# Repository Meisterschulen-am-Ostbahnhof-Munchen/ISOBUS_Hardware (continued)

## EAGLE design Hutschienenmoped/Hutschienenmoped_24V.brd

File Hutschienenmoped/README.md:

## Hutschienenmoped

<p xmlns:cc="http://creativecommons.org/ns#" xmlns:dct="http://purl.org/dc/terms/"><a property="dct:title" rel="cc:attributionURL" href="https://github.com/Meisterschulen-am-Ostbahnhof-Munchen/ISOBUS_Hardware">Hutschienenmoped</a> by <a rel="cc:attributionURL dct:creator" property="cc:attributionName" href="https://github.com/Meisterschulen-am-Ostbahnhof-Munchen">Meisterschulen am Ostbahnhof, München</a> is licensed under <a href="https://creativecommons.org/licenses/by-sa/4.0/?ref=chooser-v1" target="_blank" rel="license noopener noreferrer" style="display:inline-block;">CC BY-SA 4.0</a></p>

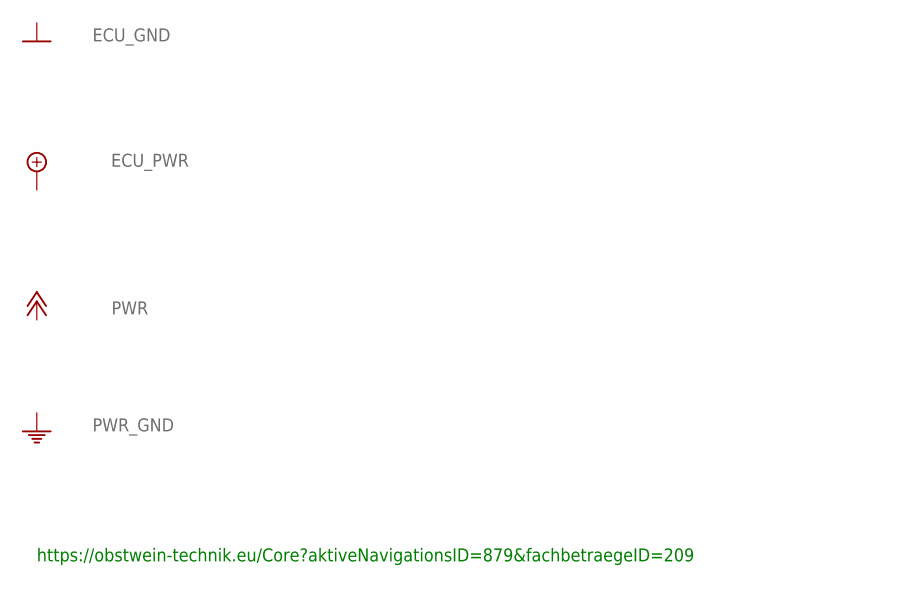
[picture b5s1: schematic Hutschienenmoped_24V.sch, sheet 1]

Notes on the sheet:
https://obstwein-technik.eu/Core?aktiveNavigationsID=879&fachbetraegeID=209

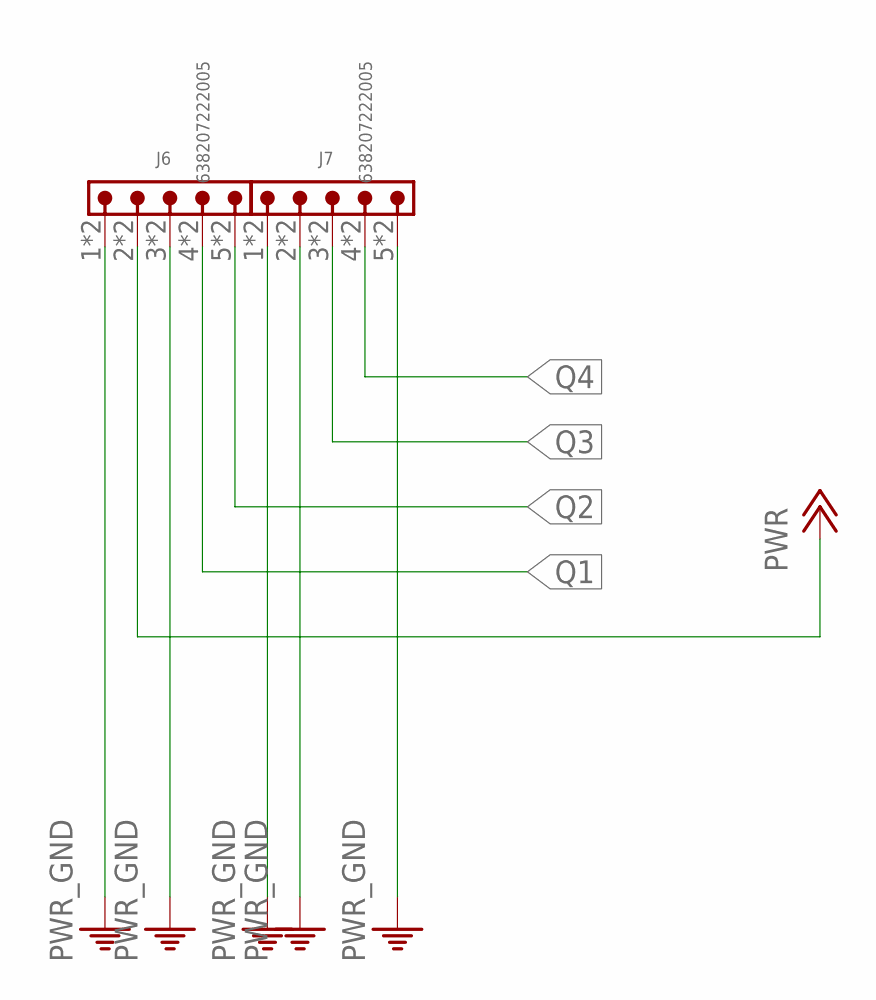
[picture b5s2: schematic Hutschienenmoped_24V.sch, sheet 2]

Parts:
J6, J7: 638207222005

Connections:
PWR: J6.2, J6.A2 (2); also elsewhere on the board
PWR_GND: J6.1, J6.3, J6.A1 (1), J6.A3 (3), J7.1, J7.2, J7.5, J7.A1 (1), J7.A2 (2), J7.A5 (5); also elsewhere on the board
Q1: J6.4, J6.A4 (4); also elsewhere on the board
Q2: J6.5, J6.A5 (5); also elsewhere on the board
Q3: J7.3, J7.A3 (3); also elsewhere on the board
Q4: J7.4, J7.A4 (4); also elsewhere on the board

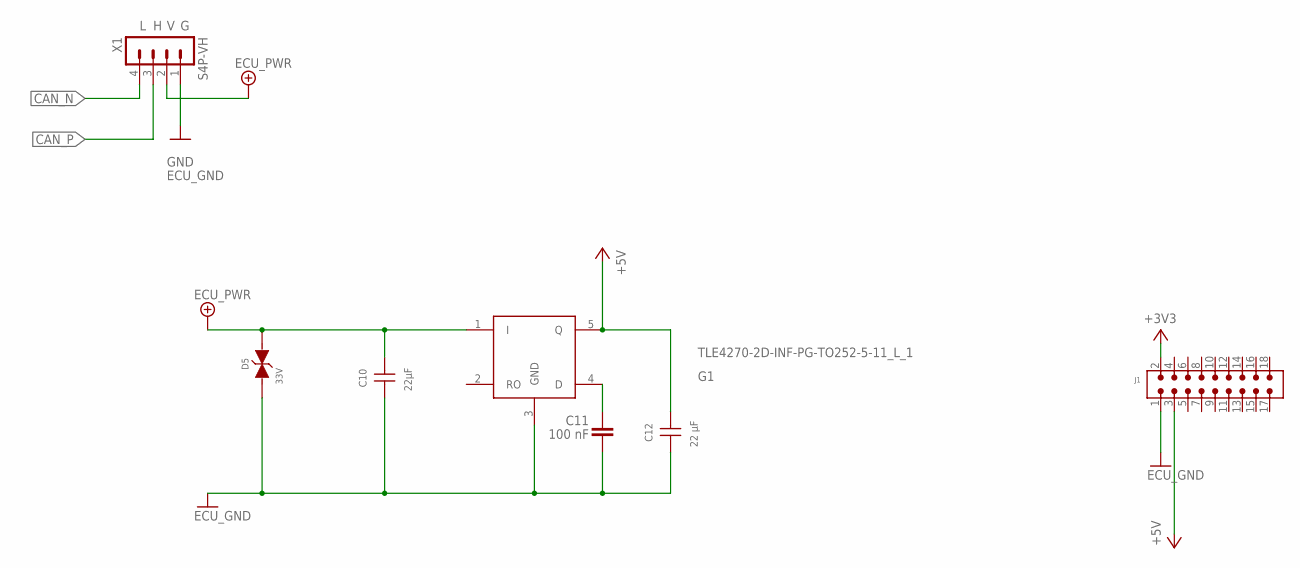
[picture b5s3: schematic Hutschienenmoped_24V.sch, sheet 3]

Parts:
C10: 22µF; WCAP-CSGP_1210_H2.5
C11: 100 nF; WCAP-CSGP_0402
C12: 22 µF; WCAP-CSGP_0805_H1.25_R
D5: 33V; WE-TVSP_DO-214AB_BIDIRECTIONAL
G1: TLE4270-2D-INF-PG-TO252-5-11_L_1; INF-PG-TO252-5-11_L_1PRIMARY
J1: 6130XX21121_61301821121; 61301821121
X1: S4P-VH

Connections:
+3V3: J1.2; also elsewhere on the board
+5V: C12.2, G1.5 (Q), J1.3; also elsewhere on the board
CAN_N: X1.4; also elsewhere on the board
CAN_P: X1.3; also elsewhere on the board
ECU_GND: C10.1, C11.2, C12.1, D5.1, G1.3 (GND), J1.1, X1.1; also elsewhere on the board
ECU_PWR: C10.2, D5.2, G1.1 (I), X1.2; also elsewhere on the board
unnamed: C11.1, G1.4 (D)

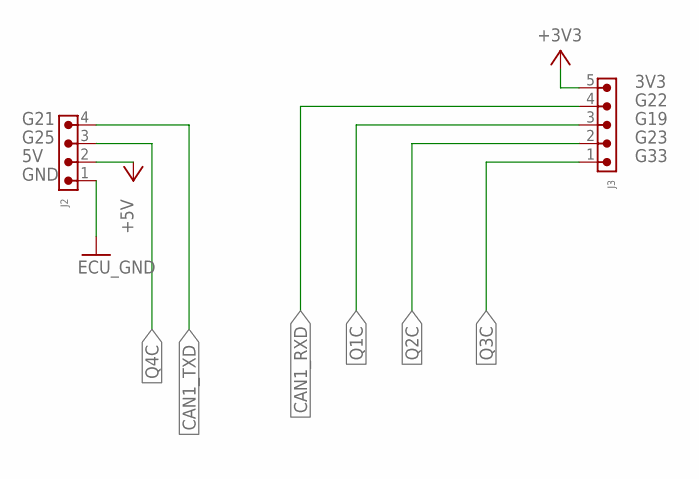
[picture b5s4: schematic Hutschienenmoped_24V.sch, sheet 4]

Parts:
J2: 6130XX11121_61300411121; 61300411121
J3: 6130XX11121_61300511121; 61300511121

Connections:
+3V3: J3.5; also elsewhere on the board
+5V: J2.2; also elsewhere on the board
CAN1_RXD: J3.4; also elsewhere on the board
CAN1_TXD: J2.4; also elsewhere on the board
ECU_GND: J2.1; also elsewhere on the board
Q1C: J3.3; also elsewhere on the board
Q2C: J3.2; also elsewhere on the board
Q3C: J3.1; also elsewhere on the board
Q4C: J2.3; also elsewhere on the board

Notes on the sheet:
GND
G25
G21
G33
G23
G19
G22
3V3

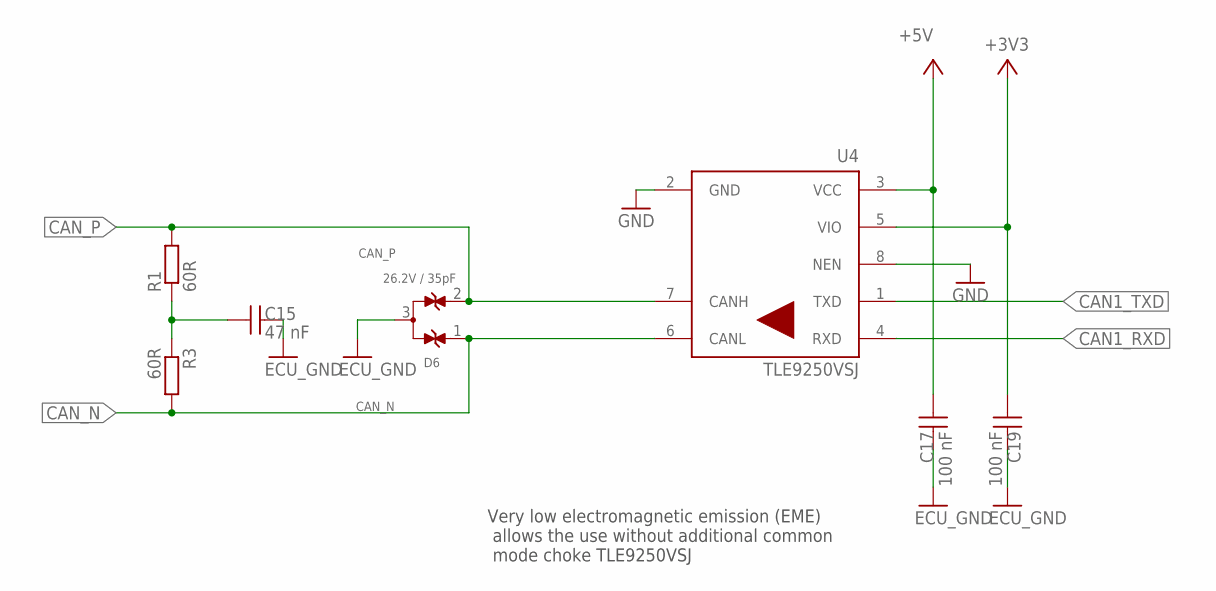
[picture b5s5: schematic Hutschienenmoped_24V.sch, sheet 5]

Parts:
C15: 47 nF; WCAP-CSGP_0805_H0.8_R
C17, C19: 100 nF; WCAP-CSGP_0805_H0.8_R
D6: 26.2V / 35pF; WE-TVS_SOT23-3L
R1, R3: 60R; R0805
U4: TLE9250VSJ; SOIC127P602X173-8N-V

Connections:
+3V3: C19.1, U4.5 (VIO); also elsewhere on the board
+5V: C17.1, U4.3 (VCC); also elsewhere on the board
CAN1_RXD: U4.4 (RXD); also elsewhere on the board
CAN1_TXD: U4.1 (TXD); also elsewhere on the board
CAN_N: D6.1, R3.2, U4.6 (CANL); also elsewhere on the board
CAN_P: D6.2, R1.2, U4.7 (CANH); also elsewhere on the board
ECU_GND: C15.2, C17.2, C19.2, D6.3, U4.2 (GND), U4.8 (NEN); also elsewhere on the board
unnamed: C15.1, R1.1, R3.1

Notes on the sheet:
Very low electromagnetic emission (EME) allows the use without additional common mode choke TLE9250VSJ

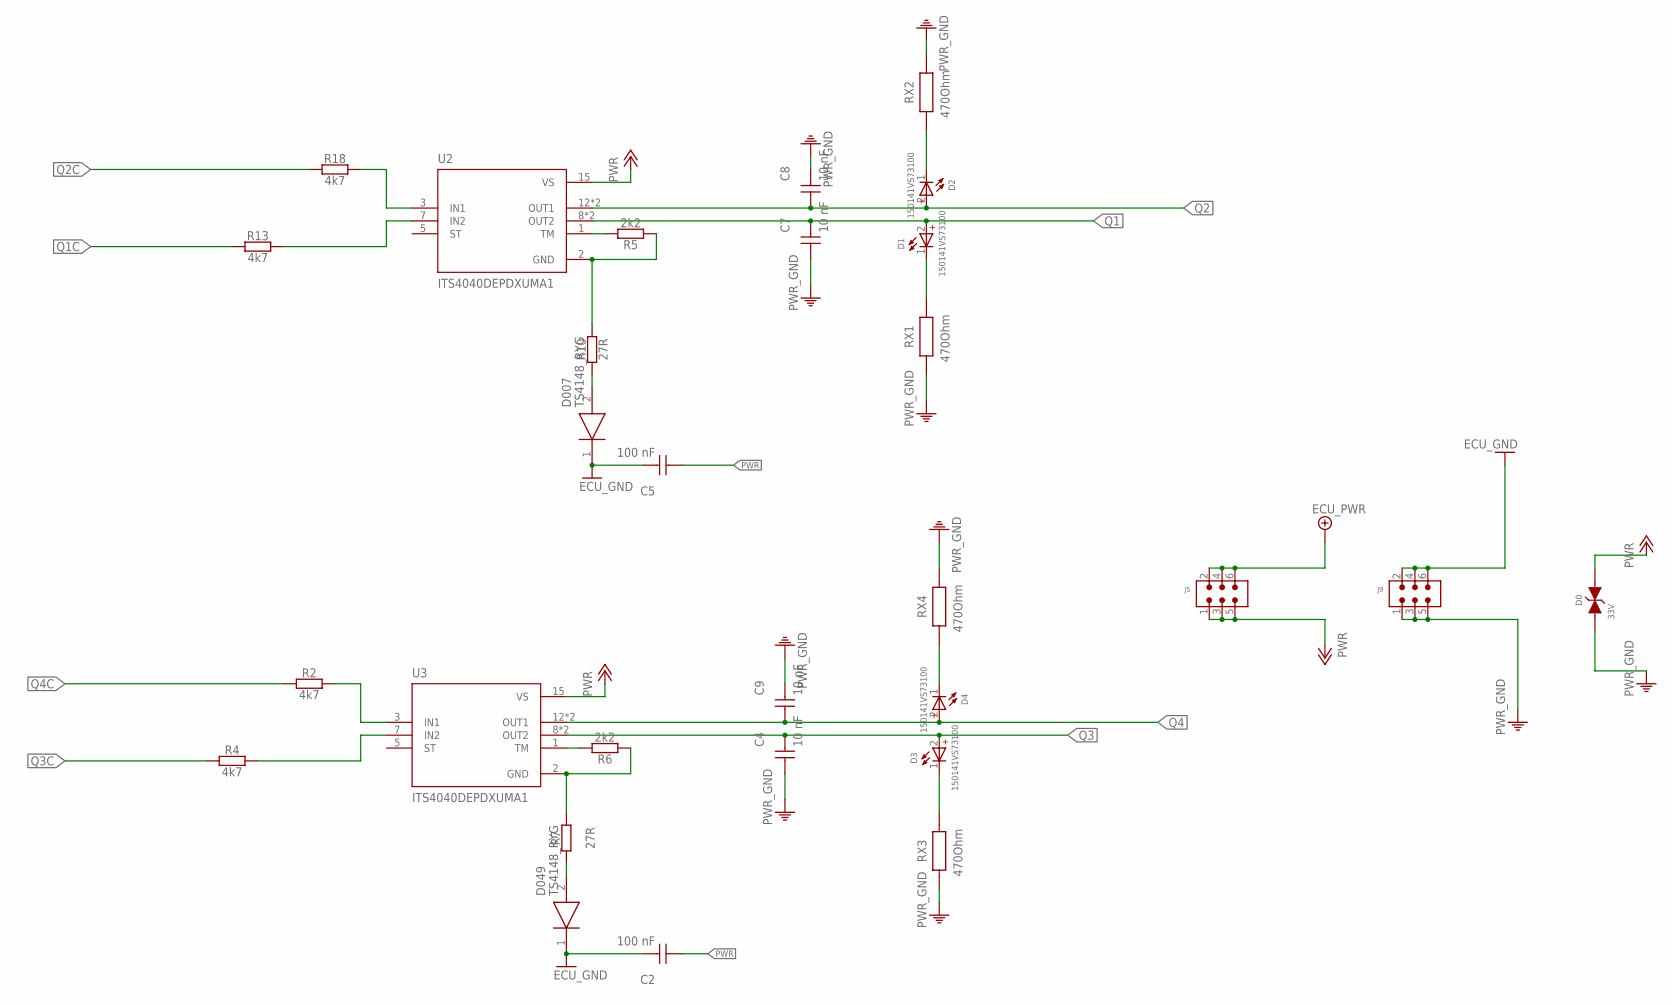
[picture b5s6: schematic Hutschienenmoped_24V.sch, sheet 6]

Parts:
C2, C5: 100 nF; WCAP-CSGP_0805_H0.8_R
C4, C7, C8, C9: 10 nF; WCAP-CSGP_0805_H0.8_R
D0: 33V; WE-TVSP_DO-214AB_BIDIRECTIONAL
D1, D2, D3, D4: 150141VS73100; WL-SMTW_3528
D007, D049: TS4148_RYG; DIOC2012X95N
J5, J9: 6130XX21121_61300621121; 61300621121
R2, R4, R13, R18: 4k7; R0805
R5, R6: 2k2; R0805
R7, R10: 27R; R0805
RX1, RX2, RX3, RX4: 470Ohm; WRIS-KWKB_0612
U2, U3: ITS4040DEPDXUMA1; SOP65P600X115-15N

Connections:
ECU_GND: C2.2, C5.2, D007.1 (K), D049.1 (K), J9.2, J9.4, J9.6; also elsewhere on the board
ECU_PWR: J5.2, J5.4, J5.6; also elsewhere on the board
unnamed: D4.1 (-), RX4.1
unnamed: R2.2, U3.3 (IN1)
unnamed: R6.2, U3.1 (TM)
unnamed: R4.2, U3.7 (IN2)
unnamed: R5.2, U2.1 (TM)
unnamed: D2.1 (-), RX2.1
unnamed: D1.1 (-), RX1.2
unnamed: D3.1 (-), RX3.2
unnamed: R18.2, U2.3 (IN1)
unnamed: D049.2 (A), R7.1
unnamed: D007.2 (A), R10.1
unnamed: R6.1, R7.2, U3.2 (GND)
unnamed: R13.2, U2.7 (IN2)
unnamed: R5.1, R10.2, U2.2 (GND)
PWR: C2.1, C5.1, D0.2, J5.1, J5.3, J5.5, U2.15 (VS), U3.15 (VS); also elsewhere on the board
PWR_GND: C4.1, C7.1, C8.2, C9.2, D0.1, J9.1, J9.3, J9.5, RX1.1, RX2.2, RX3.1, RX4.2; also elsewhere on the board
Q1: C7.2, D1.2 (+), U2.8 (OUT2), U2.10 (OUT2); also elsewhere on the board
Q1C: R13.1; also elsewhere on the board
Q2: C8.1, D2.2 (+), U2.12 (OUT1), U2.14 (OUT1); also elsewhere on the board
Q2C: R18.1; also elsewhere on the board
Q3: C4.2, D3.2 (+), U3.8 (OUT2), U3.10 (OUT2); also elsewhere on the board
Q3C: R4.1; also elsewhere on the board
Q4: C9.1, D4.2 (+), U3.12 (OUT1), U3.14 (OUT1); also elsewhere on the board
Q4C: R2.1; also elsewhere on the board

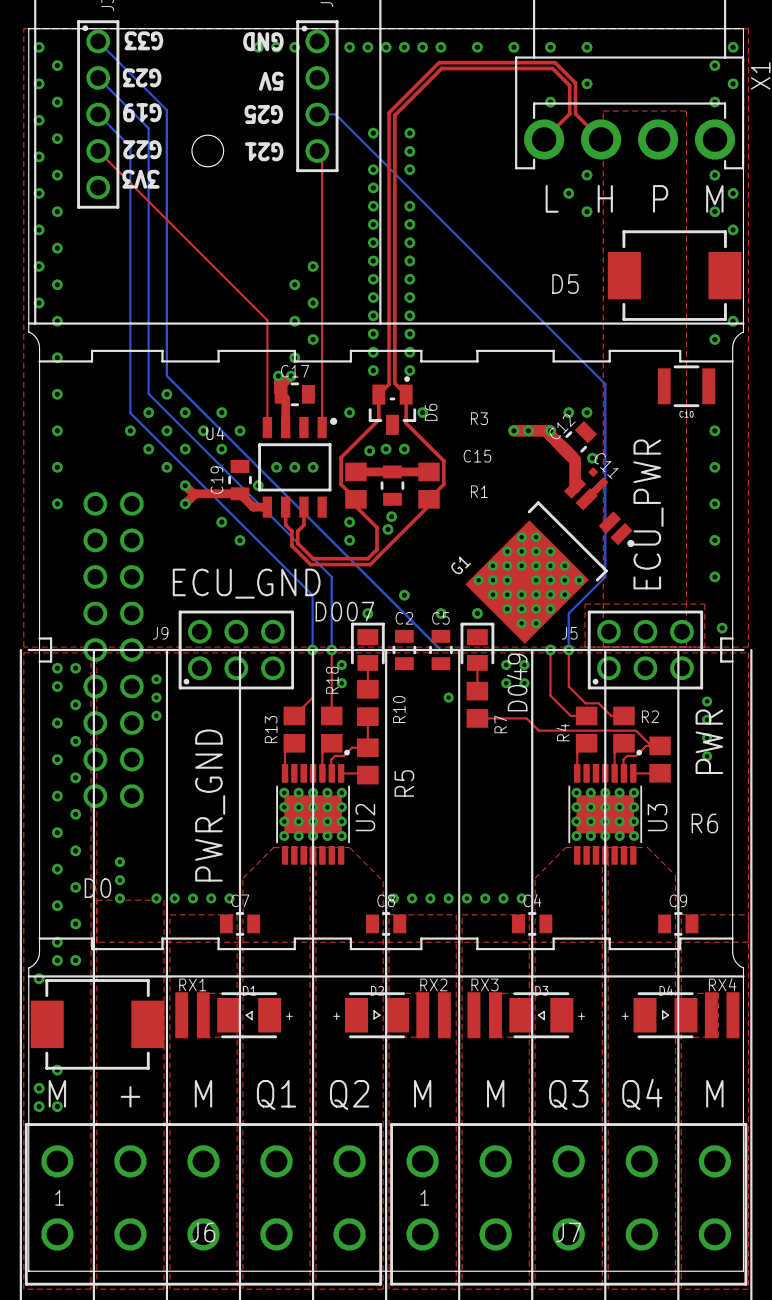
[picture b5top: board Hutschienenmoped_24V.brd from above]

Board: 4 copper layers, 49.7 x 86.4 mm, 47 parts (1 on the bottom side), 34 nets.

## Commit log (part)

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2020-08-12 just converted from https://github.com/m5stack/m5-structural-design-file/blob/master/PCB/Atomic_V1.0.PcbDoc
2020-08-13 2 Airwires
2020-08-29 collission avoid.
2020-09-29 made PDF
2020-10-15 DCDC Version
2020-10-26 Excel
2021-07-08 .. Solid Edge !
2021-07-08 outline
2021-07-08 not finished. ..
2021-07-11 ok so far ..
2021-07-11 thermals="no"
2021-07-11 Thermals off for SMD, on for THT
2021-07-11 done !
2021-07-12 Cooling of LED !
2021-07-12 so far OK !
2021-07-12 smaller LED
2021-07-12 nicer LED
2021-07-17 package adjusted to infineon recommendation
2021-07-17 thermals="no"/>
2021-07-17 ready for Produce !
2021-08-05 stick
2021-08-06 merge
2021-08-06 Order.
2021-08-06 correction !
2021-11-08 just Test
2021-11-08 8P 6P Header
2021-11-08 DTF13-4P-pcb-part-libraries
2021-11-08 Order !
2021-11-18 was a bad bug about 2 Pins.
2021-11-18 3 Versions.
2021-11-26 gitflow-feature-stash: ESP32-S3
2022-01-10 G7 for CAN RX, as G9 is a Strapping Pin.
2022-02-25 Imported from https://franz-ms-muc@github.com/Meisterschulen-am-Ostbahnhof-Munchen/ISOBUS_Hardware.git
2022-06-30 give it a Try. !
2023-04-19 cleanup
2023-04-19 supply1
2023-07-07 boms
2023-07-07 thermals="no"/>
    thermals="no"/>
2023-07-07 IFX27001TF V50.lbr
2023-07-07 verpolschutz.
2023-07-07 Prepare Prouction II
2023-07-08 intermediate commit
2023-08-04 very first draft
2023-08-04 generate 3D Model.
2023-08-04 Montagehilfe!
2023-10-16 Connector 645004114822
2023-10-20 readme
2023-11-30 Parameters of the PCB
2023-11-30 Selected BOM List
2024-02-29 Change grid unit to mm, adjust layer visibility and settings, update Fusion 360 sync status, modify wire connections and text positions.
2024-02-29 Add new 12V symbol files and update drawing settings.
2024-03-24 gitflow-feature-stash: ETH
2024-03-24 Add new wire connections and curves in the board design.
2024-03-24 Adjust wire widths and grid units, optimize for mm instead of mil.
    - Updated wire widths to 0.1 from 0.001
    - Changed grid unit distance to mm from mil
2024-03-24 Update grid distance in board file and rename connector elements: - Changed grid distance from 6mm to 22.86mm for better alignment. - Renamed connector elements J12, J14 to W1-J2, W1-J1 respectively.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
2024-03-24 Update grid distance to 32.4mm, adjust connector positions.
2024-03-24 Update grid settings, change font display, adjust pad sizes and hole drills, add new package with 10-pin socket header, modify parameter values for pads and vias. Add symbol for 10-pin socket header 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
2024-03-24 Add new layers and components for DXF, Descript, SMDround. Include a new package with description and pads. Introduce 3D package and symbol for Socket Header Bottom Entry. Create device set with deta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
2024-03-24 Update layer visibility settings for various elements.
2024-03-24 Update package description and pad positions, adjust hole sizes, and modify parameters for better PCB design. Add new contact references, wires, and signals for improved connectivity.
2024-03-24 Update Fusion 360 sync details and add new signal connections. Add text labels for USB, PRG, and PSRAM on the schematic sheet.
2024-03-24 Adjust layer visibility and polygon isolations, enhancing design clarity.
2024-03-24 Change grid unit from mil to mm, adjust polygon width, add contact references for elements J13 and J9, update via drill sizes, modify wire connections for various signals.
2024-03-24 Change grid settings to 50mm, hide grid display. Simplify wire connections in the layout for better clarity and organization. Adjust polygon widths for consistency and isolate values. Add vias for im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
2024-03-24 Update vias and wires coordinates for better routing efficiency.
    - Adjusted via positions for improved connectivity.
    - Modified wire paths to optimize signal flow.
2024-03-24 Add resistors R14 and R15, update wiring connections. - Added resistors R14 and R15 with values of 13K. - Updated wiring connections for resistors R14 and R15 in the schematic and board files.
2024-03-24 Add new components and quantities to CSV file. - Include various resistors, capacitors, diodes, headers. - Update existing entries with detailed descriptions.
2024-03-24 Change grid distance to 50 mil, update layer visibility settings. Adjust text and wire placements for clarity. Update package library versions for footprints.
2024-03-24 Adjust layer visibility settings and add new wires in the design.
2024-03-24 NOT correct !
2024-03-24 Update grid distance to 70mm, layer visibility adjustments.
2024-03-24 Update FusionSync revision ID and VIA coordinates
    Changed the FusionSync revision ID in the board file. Adjusted VIA coordinates for accuracy.
2024-03-24 Add new components and connections for XL_2ETH module. Update resistors, capacitors, diodes, and IC placements. Include mounting points for M3 screws.
2024-03-24 Update Fusion 360 sync timestamps and add mounting holes.
2024-03-24 Remove outdated zip files for Hutschienenmoped-XL.
2024-03-24 Add new 12V version for Hutschienenmoped-XL
    A new 12V version of the Hutschienenmoped-XL has been added.
2024-03-24 Update grid and add circles and wires for potentiometers. Adjust FusionSync settings.
2024-03-24 Update grid settings and layer visibility, modify library descriptions, and adjust package details.
2024-03-24 Update FusionSync details in board file and add new zip file for 2024-03-24.
2024-03-24 Add new board file with layers and library information.
    - Added a new board file with multiple layers for design elements.
    - Included library information for Wurth_Connectors_WR-TBL Rising Cage Clamp.
2024-03-25 Remove outdated button board zip files
    Deleted two old binary files of button boards.
2024-03-25 Add new accessory board file for XL accessories.
    A new accessory board file has been added for XL accessories.
2024-03-25 Add new accessory board for 4 buttons.
2024-03-25 Remove outdated zip file for Board_4_Poti.
2024-03-25 Change grid distance and layer visibility settings, update hole placements, adjust wire positions, and modify approved hash values.
2024-03-25 Remove outdated zip file.
    Deleted an old zip file that was no longer needed.
2024-03-25 Update BOM file with new changes.
    Binary files differ.
2024-03-25 Rename zip file for Hutschienenmoped-XL to new date version.
2024-03-25 Update Excel files with changes in Hutschienenmoped-XL folder.
2024-07-07 Update screen resolution and component details in CSV file.
2024-07-07 Update screen resolution and wire connections in multiple board files.
    - Update screen resolution from "4480 1444" to "7040 1440".
    - Adjust wire connections coordinates in multiple places for consistency.
2024-07-07 Update connector element position and wire coordinates in board design file
    The commit updates the position of a connector element and adjusts wire coordinates in the board design file.
2024-07-07 Update schematic and board editor settings for Board_4_Buttons.
2024-07-07 Update via stop limit to 4mm in multiple board files
    Changed the via stop limit parameter value from 0mil to 4mm in several board files for consistency. Adjusted view settings in eagle.epf file.
2024-07-07 not good !
2024-07-07 Update thermal settings for components in multiple packages. Set thermals to "no" for all SMD components in various footprints to optimize thermal performance and behavior during operation.
2024-07-16 Add new CAD files for various geometric shapes and patterns.
2024-07-16 Update grid settings to use millimeters instead of mils, adjust layer visibility, add holes and Fusion synchronization feature compatibility note. Refine circle positions and wire paths in DXF import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
2024-07-16 Change setting to not use vector font, update circle and wire elements with width set to 0 in board file.
2024-07-16 Update wire curve in Platte_1.brd file
    Adjusted wire curve value for better alignment.
2024-07-16 Update wire coordinates for smoother curve transition.
    Adjusted wire positions for better alignment and curve flow.
2024-07-16 Update wire coordinates and add new wires and circles.
2024-07-16 Update board editor settings and layers, add new windows for schematic and board editors, change font setting to vector font.
2024-07-25 Update LICENSE
2024-10-04 Add new 3D models for board accessories - Added multiple new 3D model files for board accessories.
2024-10-04 gitflow-feature-stash: prot Add SMA_DO-214AC package, elements D014 to D023 with attributes, and resistors R35 to R38. Update classes Ampere7 and clearance values. Include wire connections for new el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
2024-10-04 Update SMD components with no thermal relief - Modify SMD components to remove thermal relief for better performance.
2024-10-04 Change font setting to not always vector, adjust capacitor element attributes. Update diode elements' positions and attributes.
2024-10-04 Update Excel files for Hutschienenmoped-XL.
2024-10-06 Add two new images for Hutschienenmoped-XL. New visual assets added.
2024-10-06 Rename Hauptplatine files from specific names to a generic one.
2024-10-25 Update screen resolution and hole drill sizes, change font setting in eagle.epf and Platte_1.brd.
2024-11-01 Add new zip file for Hutschienenmoped-XL plate. New zip file added for a component in the project.
2024-11-01 Add new DXF files for different parts of the project. Update file content with various sections like HEADER, TABLES, BLOCKS, ENTITIES, and OBJECTS containing specific data structures and entities.
2024-11-01 Add Eagle version "09 06 02" to multiple files.
2024-11-01 Delete unnecessary library references from configuration.
    Removed a large number of unused library references from the configuration file to streamline and declutter the project setup.
2024-11-01 Update Eagle version and add multiple library URNs. Detailed description: Update the Eagle version to "09 06 02" and include various library URNs in the configuration file.
2024-11-01 Add dxfimport script files and board layouts for top left and top right bars.
    - Added dxfimport script files for top left and top right bars
    - Updated board layouts with wire connections and circles
2024-11-01 Add new top rail components for XL model. Detailed changes include adding files for left and right top rails A and B in the 2024-11-01 zip format.
2025-02-27 Update FusionSync settings and add text label on the board.
    - Updated FusionSync PCBGuid attribute
    - Added a text label "R" at coordinates (-50.8, -13.97)
2025-02-27 Rename file to update date in filename.
2025-02-27 Rename file to update date in filename
    Changed the filename to reflect the updated date for clarity.
2025-02-27 Adjust layer visibility and fill settings for multiple layers.
2025-02-27 Rename file to update version from October 2024 to February 2025.
2025-03-01 Update font setting to not always use vector font and adjust FusionSync details in board file.
2025-03-01 Update screen resolution in eagle.epf
    Changed screen resolution from 7040x1440 to 1920x1080 for better display.
2025-10-10 Updates resistor values and library URNs
    Changes resistor values from 13k to 22k.
    Updates library URNs in the eagle project file and board file.
    Sets linktopcb3d to false in the board file.
2025-12-18 Revises README for enhanced clarity and navigation
    Introduces structured Markdown elements to improve readability and
    includes direct links for better access to documentation and source
    directories. Adds OSHWA certification information for Hutschienenmoped XL
    and visually represents licensing with Creative Commons badge.
    Enhances user experience by providing comprehensive project details.
